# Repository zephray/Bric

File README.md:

Bric
====

Bric is the codename for my course project design for EE-300 at Penn State. It is a portable digital audio player. It was evolved from my previous project RhythmPocketLite, and the code has been used as base for my next project called Fobu. The code hosted here is likely broken and won't compile and is only here for archive purposes.

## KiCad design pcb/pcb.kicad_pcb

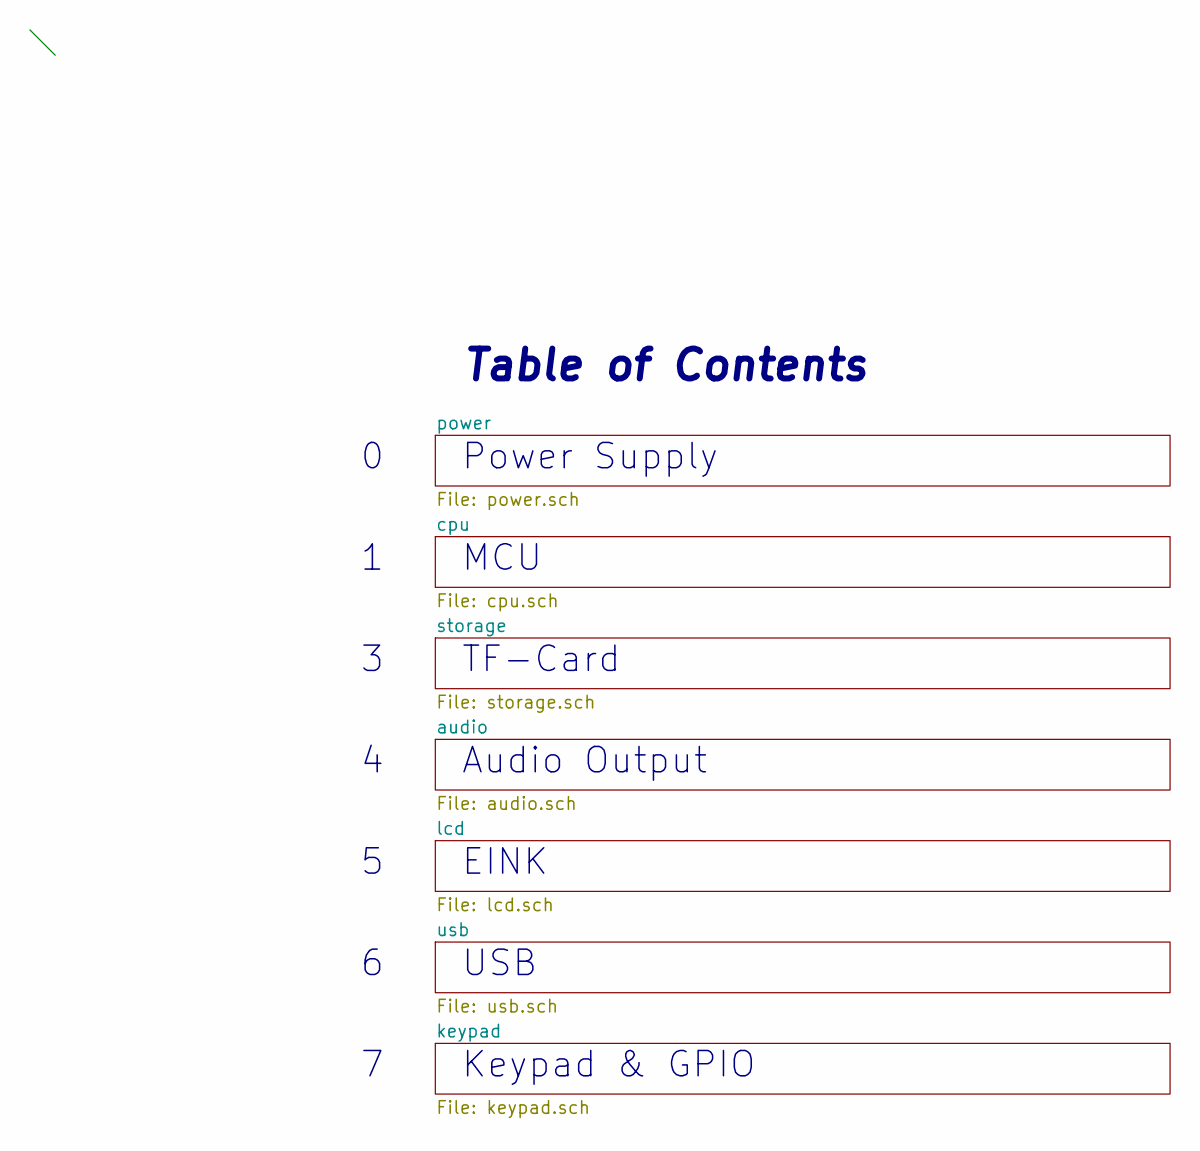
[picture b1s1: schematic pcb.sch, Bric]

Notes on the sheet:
MCU
EINK
TF-Card
Table of Contents
Power Supply
Audio Output
Keypad & GPIO
USB

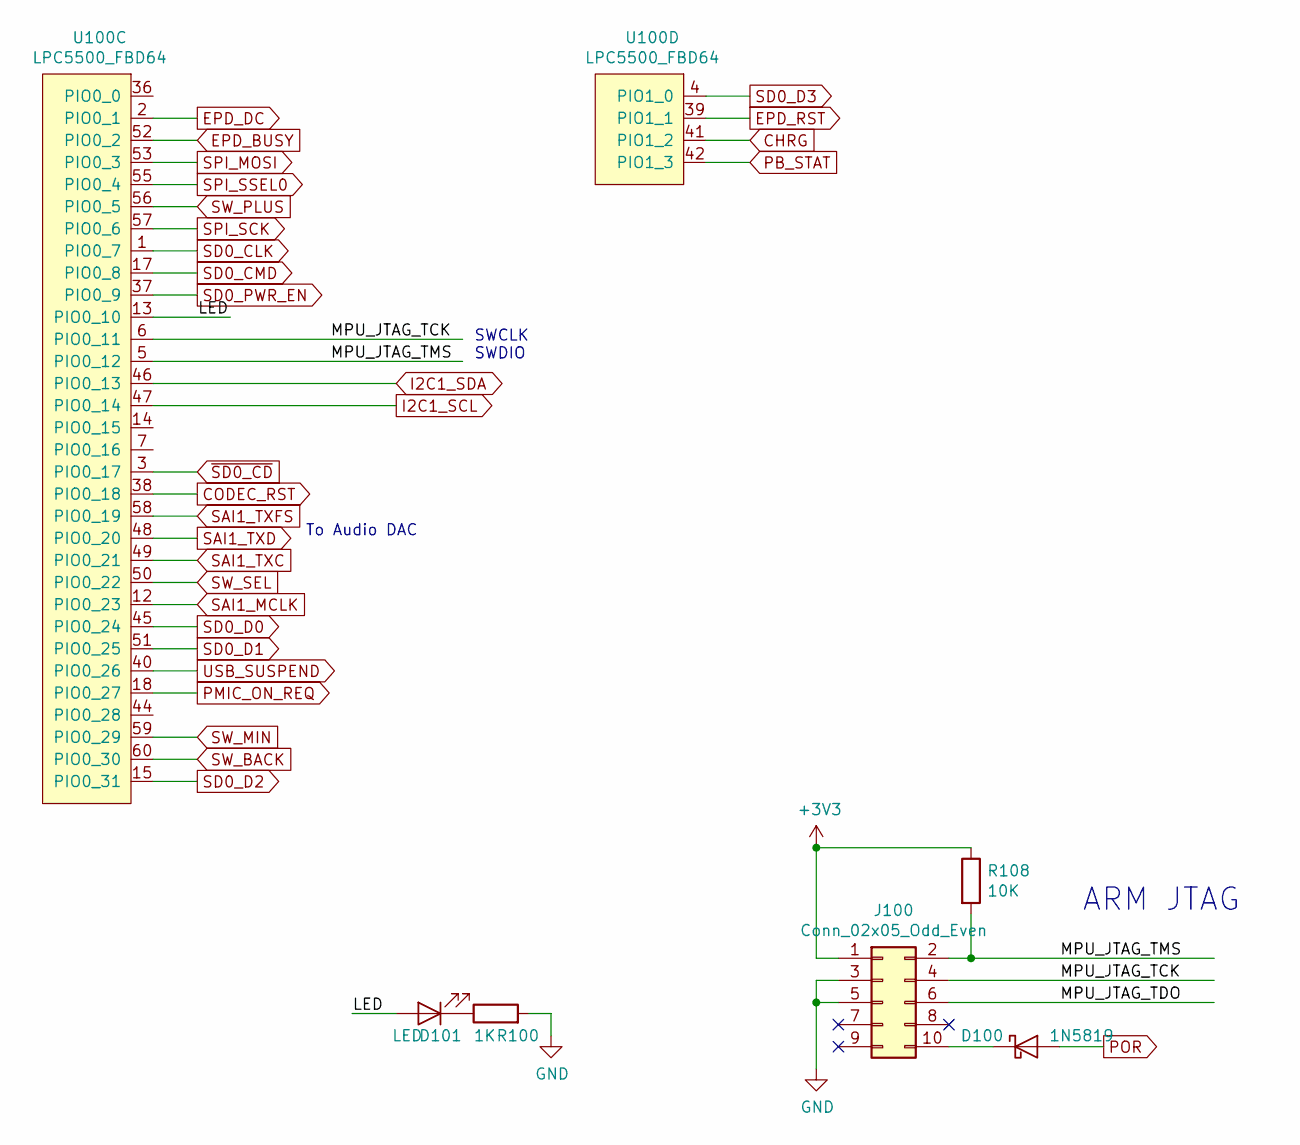
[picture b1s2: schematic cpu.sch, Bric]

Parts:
D100: 1N5819; D_SOD-123
D101: LED; LED_0603_1608Metric
J100: Conn_02x05_Odd_Even; PinHeader_2x05_P1.27mm_Vertical_SMD
R100: 1K; R_0603_1608Metric
R108: 10K; R_0603_1608Metric
U100: LPC5500_FBD64; LQFP-64-1EP_10x10mm_P0.5mm_EP5x5mm_ThermalVias

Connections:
/cpu/LED: D101.2 (A), U100.13 (PIO0_10)
/cpu/MPU_JTAG_TCK: J100.4, U100.6 (PIO0_11)
/cpu/MPU_JTAG_TMS: J100.2, R108.2, U100.5 (PIO0_12)
CHRG: U100.41 (PIO1_2); also elsewhere on the board
CODEC_RST: U100.38 (PIO0_18); also elsewhere on the board
EPD_BUSY: U100.52 (PIO0_2); also elsewhere on the board
EPD_DC: U100.2 (PIO0_1); also elsewhere on the board
EPD_RST: U100.39 (PIO1_1); also elsewhere on the board
I2C1_SCL: U100.47 (PIO0_14); also elsewhere on the board
I2C1_SDA: U100.46 (PIO0_13); also elsewhere on the board
unnamed: D100.1 (K), J100.10
unnamed: D101.1 (K), R100.1
PB_STAT: U100.42 (PIO1_3); also elsewhere on the board
PMIC_ON_REQ: U100.18 (PIO0_27); also elsewhere on the board
POR: D100.2 (A); also elsewhere on the board
SAI1_MCLK: U100.12 (PIO0_23); also elsewhere on the board
SAI1_TXC: U100.49 (PIO0_21); also elsewhere on the board
SAI1_TXD: U100.48 (PIO0_20); also elsewhere on the board
SAI1_TXFS: U100.58 (PIO0_19); also elsewhere on the board
SD0_CLK: U100.1 (PIO0_7); also elsewhere on the board
SD0_CMD: U100.17 (PIO0_8); also elsewhere on the board
SD0_D0: U100.45 (PIO0_24); also elsewhere on the board
SD0_D1: U100.51 (PIO0_25); also elsewhere on the board
SD0_D2: U100.15 (PIO0_31); also elsewhere on the board
SD0_D3: U100.4 (PIO1_0); also elsewhere on the board
SPI_MOSI: U100.53 (PIO0_3); also elsewhere on the board
SPI_SCK: U100.57 (PIO0_6); also elsewhere on the board
SPI_SSEL0: U100.55 (PIO0_4); also elsewhere on the board
SW_BACK: U100.60 (PIO0_30); also elsewhere on the board
SW_MIN: U100.59 (PIO0_29); also elsewhere on the board
SW_PLUS: U100.56 (PIO0_5); also elsewhere on the board
SW_SEL: U100.50 (PIO0_22); also elsewhere on the board
USB_SUSPEND: U100.40 (PIO0_26); also elsewhere on the board
~SD0_CD: U100.3 (PIO0_17); also elsewhere on the board

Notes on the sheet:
ARM JTAG
To Audio DAC
SWCLK SWDIO

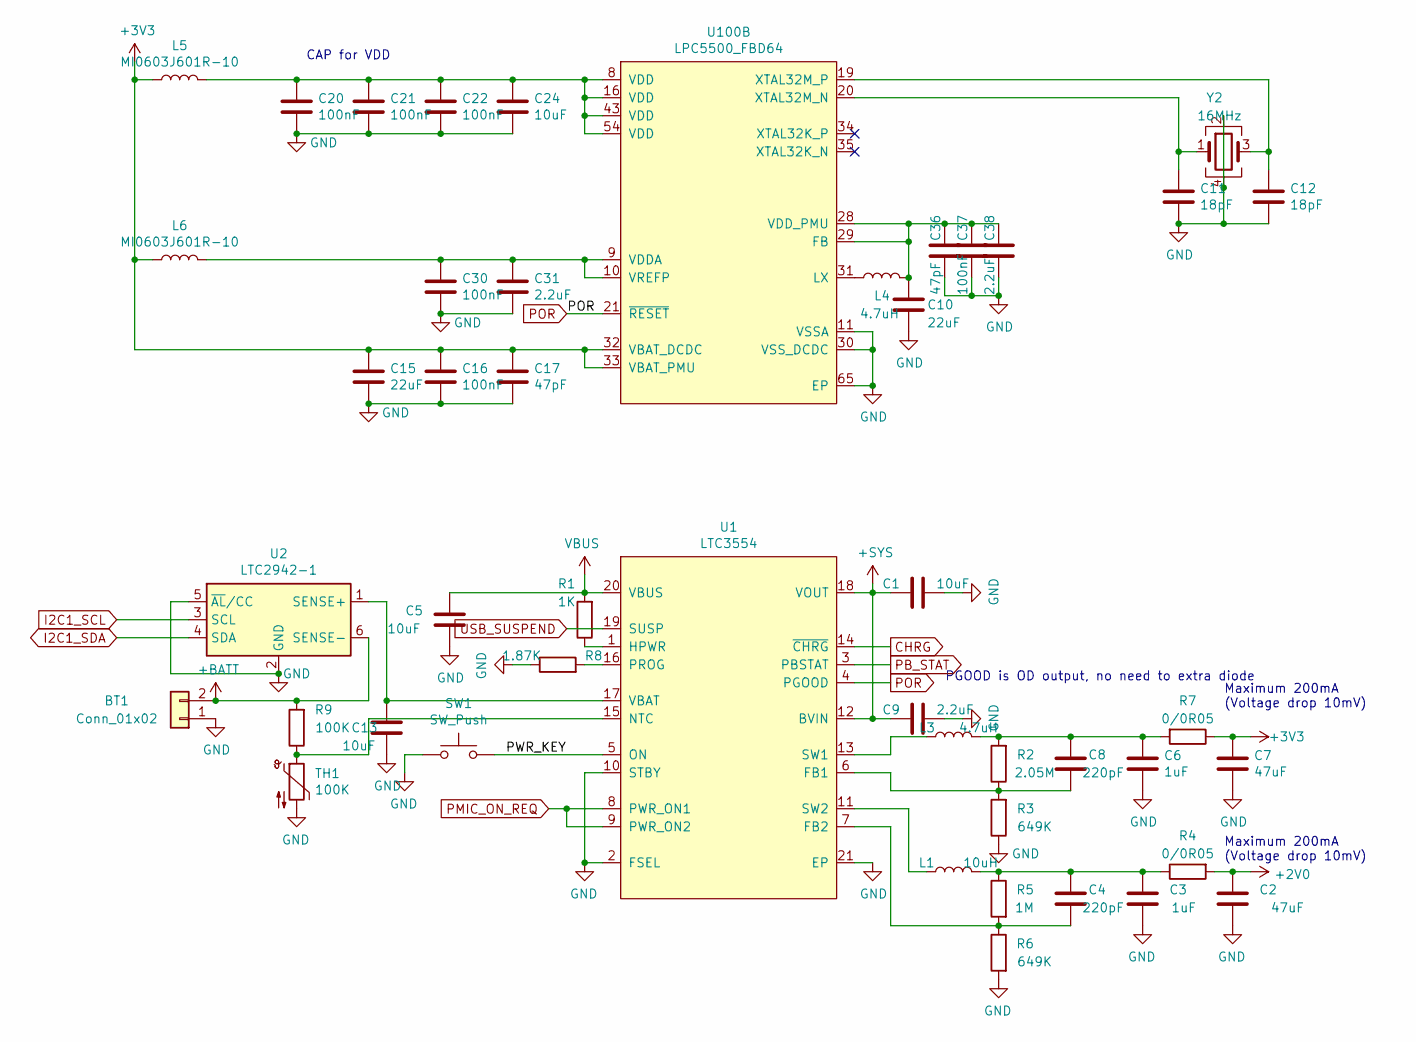
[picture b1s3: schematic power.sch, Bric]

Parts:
BT1: Conn_01x02; Molex_PicoBlade_53261-0271_1x02-1MP_P1.25mm_Horizontal
C1, C5, C13, C24: 10uF; C_0603_1608Metric
C2, C7: 47uF; C_0805_2012Metric
C3, C6: 1uF; C_0402_1005Metric
C4, C8: 220pF; C_0402_1005Metric
C9, C31, C38: 2.2uF; C_0402_1005Metric
C10, C15: 22uF; C_0603_1608Metric
C11, C12: 18pF; C_0402_1005Metric
C16, C20, C21, C22, C30, C37: 100nF; C_0402_1005Metric
C17, C36: 47pF; C_0402_1005Metric
L1: 10uH; L_Vishay_IHLP-1212
L3, L4: 4.7uH; L_Vishay_IHLP-1212
L5, L6: MI0603J601R-10; L_0603_1608Metric
R1: 1K; R_0603_1608Metric
R2: 2.05M; R_0603_1608Metric
R3, R6: 649K; R_0603_1608Metric
R4, R7: 0/0R05; R_0805_2012Metric
R5: 1M; R_0603_1608Metric
R8: 1.87K; R_0603_1608Metric
R9: 100K; R_0603_1608Metric
SW1: SW_Push; SW_SPST_EVQP7C
TH1: 100K; R_0603_1608Metric
U1: LTC3554; VQFN-20-1EP_3x3mm_P0.4mm_EP1.7x1.7mm_ThermalVias
U2: LTC2942-1; DFN-6-1EP_3x2mm_P0.5mm_EP1.65x1.35mm
U100: LPC5500_FBD64; LQFP-64-1EP_10x10mm_P0.5mm_EP5x5mm_ThermalVias
Y2: 16MHz; Oscillator_SMD_Abracon_ASE-4Pin_3.2x2.5mm

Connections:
+2V0: C2.1, R4.2; also elsewhere on the board
+BATT: BT1.2, R9.2, U2.6 (SENSE-)
+SYS: C1.2, C9.2, U1.12 (BVIN), U1.18 (VOUT); also elsewhere on the board
/power/PWR_KEY: SW1.2, U1.5 (ON)
CHRG: U1.14 (~CHRG); also elsewhere on the board
I2C1_SCL: U2.3 (SCL); also elsewhere on the board
I2C1_SDA: U2.4 (SDA); also elsewhere on the board
unnamed: C3.1, C4.1, L1.1, R4.1, R5.1
unnamed: C4.2, R5.2, R6.1, U1.7 (FB2)
unnamed: C6.1, C8.1, L3.2, R2.2, R7.2
unnamed: C8.2, R2.1, R3.2, U1.6 (FB1)
unnamed: C10.1, C36.1, C37.1, C38.1, L4.2, U100.28 (VDD_PMU), U100.29 (FB)
unnamed: C11.1, U100.20 (XTAL32M_N), Y2.1
unnamed: C12.1, U100.19 (XTAL32M_P), Y2.3
unnamed: C13.1, U1.17 (VBAT), U2.1 (SENSE+)
unnamed: C20.1, C21.1, C22.1, C24.1, L5.2, U100.8 (VDD), U100.16 (VDD), U100.43 (VDD), U100.54 (VDD)
unnamed: C30.1, C31.1, L6.2, U100.9 (VDDA), U100.10 (VREFP)
unnamed: L1.2, U1.11 (SW2)
unnamed: L3.1, U1.13 (SW1)
unnamed: L4.1, U100.31 (LX)
unnamed: R1.1, U1.1 (HPWR)
unnamed: R8.2, U1.16 (PROG)
unnamed: R9.1, TH1.1, U1.15 (NTC)
PB_STAT: U1.3 (PBSTAT); also elsewhere on the board
PMIC_ON_REQ: U1.8 (PWR_ON1), U1.9 (PWR_ON2); also elsewhere on the board
POR: U1.4 (PGOOD), U100.21 (~RESET); also elsewhere on the board
USB_SUSPEND: U1.19 (SUSP); also elsewhere on the board
VBUS: C5.1, R1.2, U1.20 (VBUS); also elsewhere on the board

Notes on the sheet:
Maximum 200mA (Voltage drop 10mV)
CAP for VDD
PGOOD is OD output, no need to extra diode

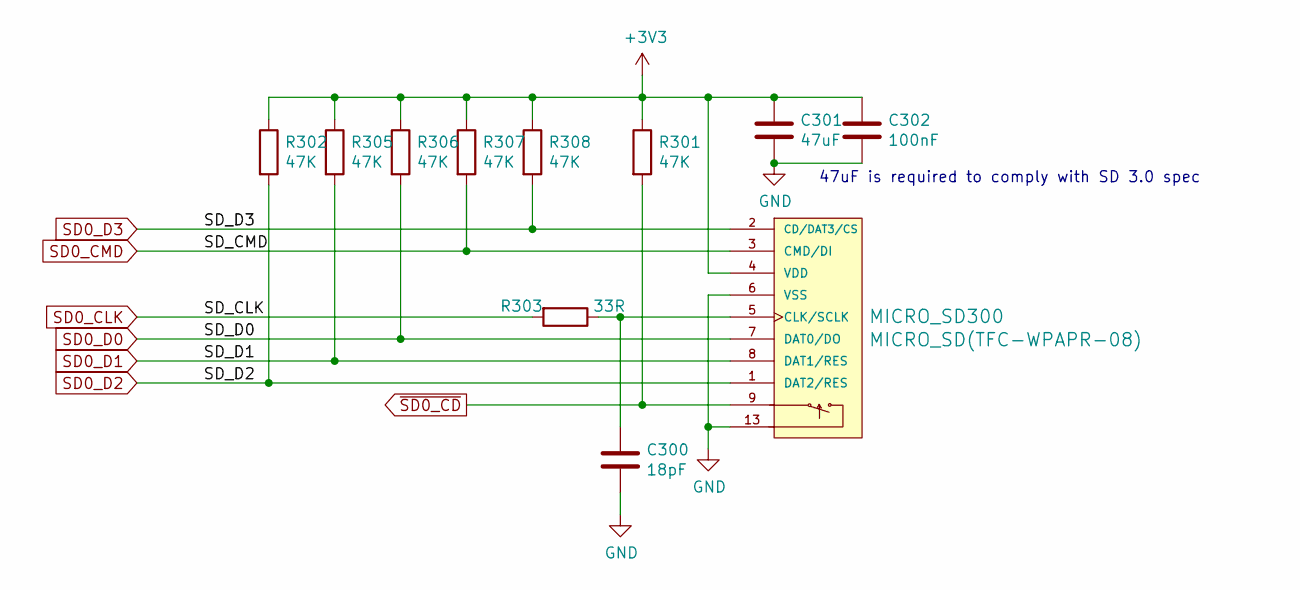
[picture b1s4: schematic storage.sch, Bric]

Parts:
C300: 18pF; C_0402_1005Metric
C301: 47uF; C_0805_2012Metric
C302: 100nF; C_0402_1005Metric
MICRO_SD300: MICRO_SD(TFC-WPAPR-08); TFC-WPAPR-08
R301, R302, R305, R306, R307, R308: 47K; R_0402_1005Metric
R303: 33R; R_0402_1005Metric

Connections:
unnamed: C300.1, MICRO_SD300.5 (CLK/SCLK), R303.1
SD0_CLK: R303.2; also elsewhere on the board
SD0_CMD: MICRO_SD300.3 (CMD/DI), R307.2; also elsewhere on the board
SD0_D0: MICRO_SD300.7 (DAT0/DO), R306.2; also elsewhere on the board
SD0_D1: MICRO_SD300.8 (DAT1/RES), R305.2; also elsewhere on the board
SD0_D2: MICRO_SD300.1 (DAT2/RES), R302.2; also elsewhere on the board
SD0_D3: MICRO_SD300.2 (CD/DAT3/CS), R308.2; also elsewhere on the board
~SD0_CD: MICRO_SD300.9, R301.2; also elsewhere on the board

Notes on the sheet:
47uF is required to comply with SD 3.0 spec

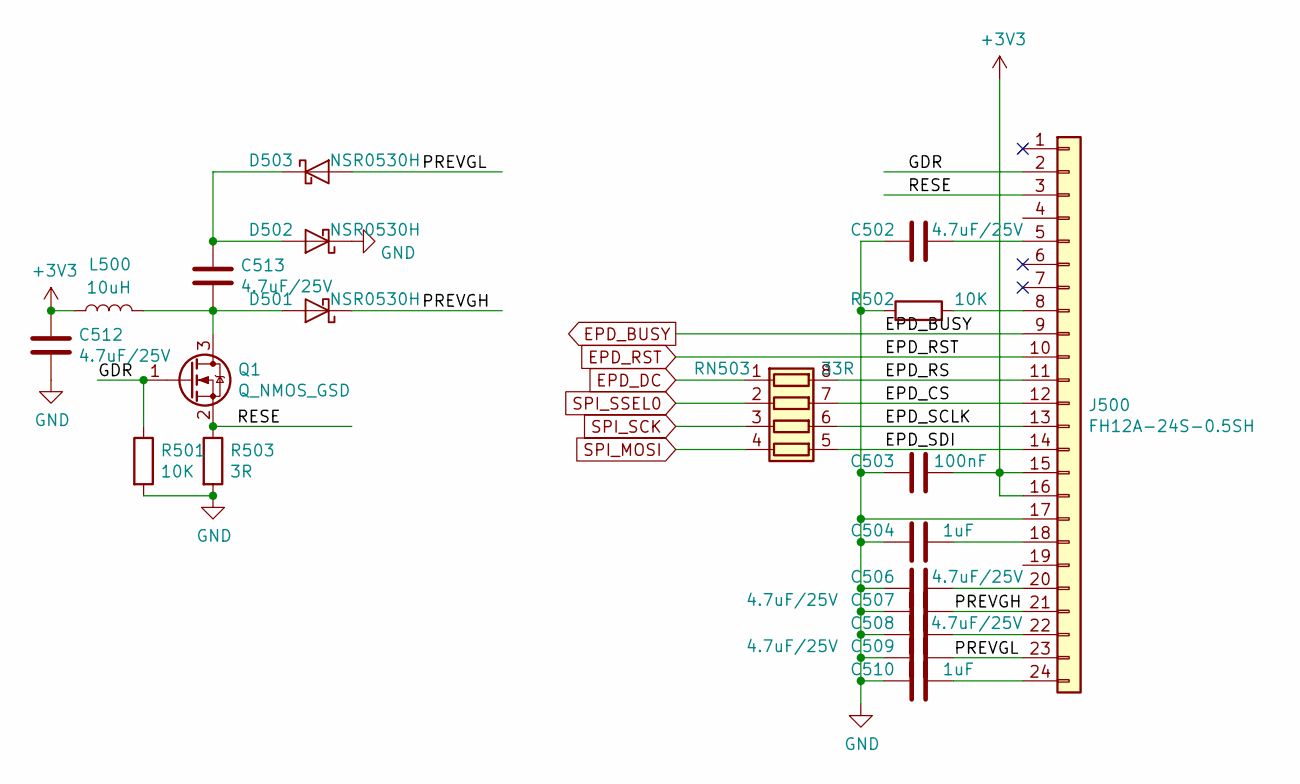
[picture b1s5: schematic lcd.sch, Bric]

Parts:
C502, C506, C507, C508, C509, C512, C513: 4.7uF/25V; C_0805_2012Metric
C503: 100nF; C_0402_1005Metric
C504, C510: 1uF; C_0603_1608Metric
D501, D502, D503: NSR0530H; D_SOD-323
J500: FH12A-24S-0.5SH; Hirose_FH12A-24S-0.5SH_1x24-1MP_P0.50mm_Horizontal
L500: 10uH; L_Vishay_IHLP-1212
Q1: Q_NMOS_GSD; SOT-323_SC-70
R501, R502: 10K; R_0603_1608Metric
R503: 3R; R_0603_1608Metric
RN503: 33R; R_Array_Convex_4x0402

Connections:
/lcd/EPD_CS: J500.12, RN503.7 (R2.2)
/lcd/EPD_RS: J500.11, RN503.8 (R1.2)
/lcd/EPD_SCLK: J500.13, RN503.6 (R3.2)
/lcd/EPD_SDI: J500.14, RN503.5 (R4.2)
/lcd/GDR: J500.2, Q1.1 (G), R501.1
/lcd/PREVGH: C507.2, D501.1 (K), J500.21
/lcd/PREVGL: C509.1, D503.2 (A), J500.23
/lcd/RESE: J500.3, Q1.2 (S), R503.1
EPD_BUSY: J500.9; also elsewhere on the board
EPD_DC: RN503.1 (R1.1); also elsewhere on the board
EPD_RST: J500.10; also elsewhere on the board
unnamed: C502.2, J500.5
unnamed: C504.2, J500.18
unnamed: C506.2, J500.20
unnamed: C508.1, J500.22
unnamed: C510.1, J500.24
unnamed: C513.1, D501.2 (A), L500.2, Q1.3 (D)
unnamed: C513.2, D502.2 (A), D503.1 (K)
unnamed: J500.8, R502.2
SPI_MOSI: RN503.4 (R4.1); also elsewhere on the board
SPI_SCK: RN503.3 (R3.1); also elsewhere on the board
SPI_SSEL0: RN503.2 (R2.1); also elsewhere on the board

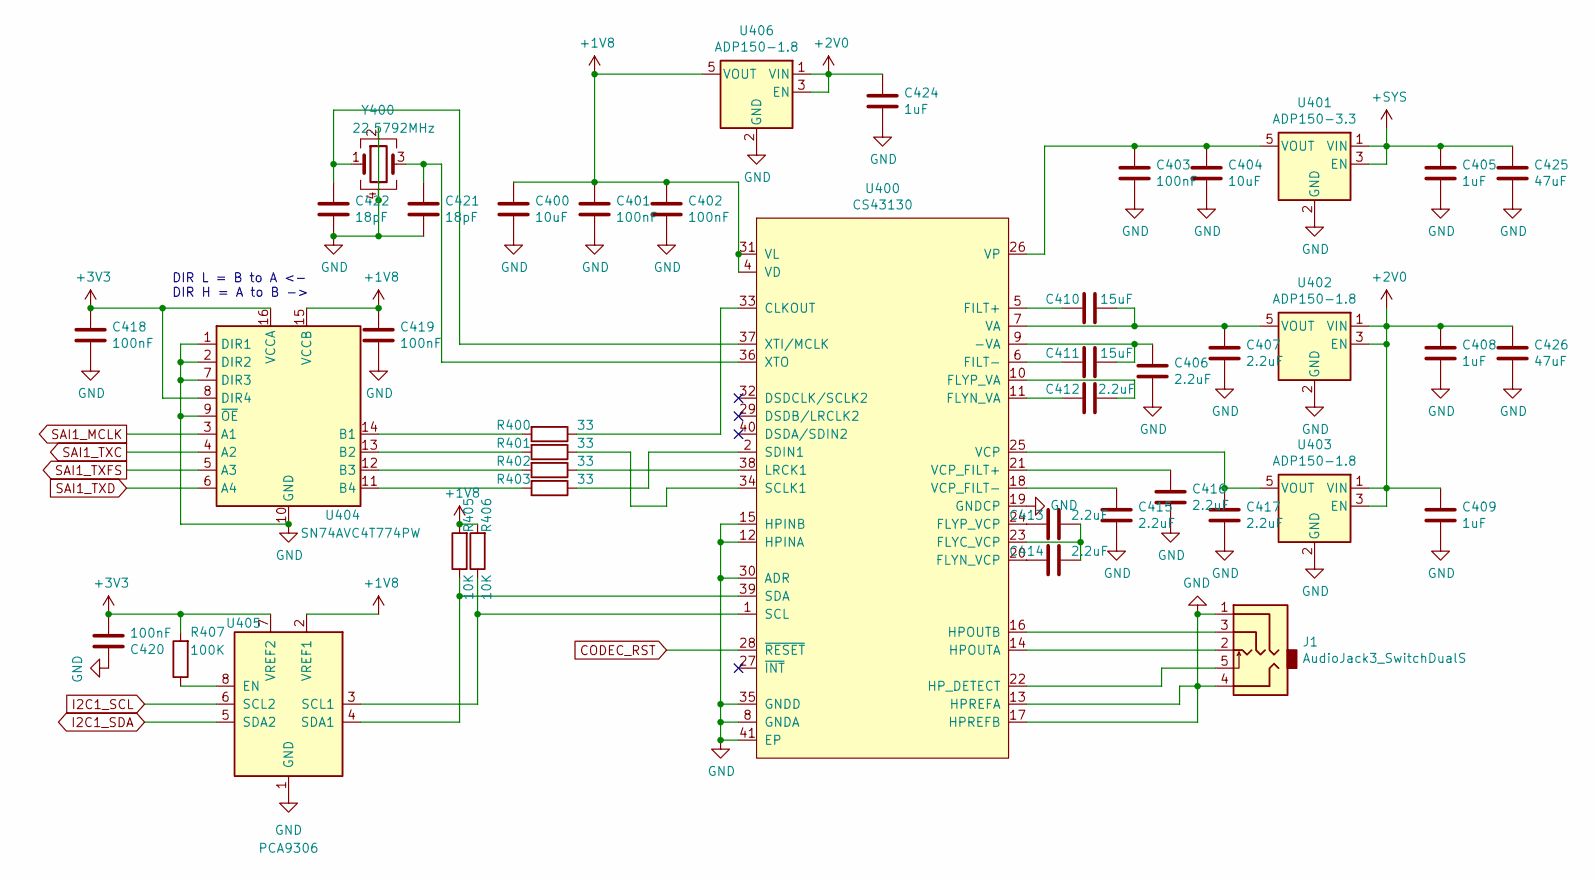
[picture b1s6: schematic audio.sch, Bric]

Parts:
C400: 10uF; C_0402_1005Metric
C401, C402, C403, C418, C419, C420: 100nF; C_0402_1005Metric
C404: 10uF; C_0603_1608Metric
C405, C408, C409, C424: 1uF; C_0402_1005Metric
C406, C407, C412, C413, C414, C415, C416, C417: 2.2uF; C_0402_1005Metric
C410, C411: 15uF; C_0603_1608Metric
C421, C422: 18pF; C_0402_1005Metric
C425, C426: 47uF; C_0805_2012Metric
J1: AudioJack3_SwitchDualS; Jack_3.5mm_PJ327E_5A
R400, R401, R402, R403: 33; R_0402_1005Metric
R405, R406: 10K; R_0603_1608Metric
R407: 100K; R_0603_1608Metric
U400: CS43130; QFN-40-1EP_5x5mm_P0.4mm_EP3.6x3.6mm_ThermalVias
U401: ADP150-3.3; SOT-23-5
U402, U403, U406: ADP150-1.8; SOT-23-5
U404: SN74AVC4T774PW; TSSOP-16_4.4x5mm_P0.65mm
U405: PCA9306; VSSOP-8_2.3x2mm_P0.5mm
Y400: 22.5792MHz; Oscillator_SMD_Abracon_ASE-4Pin_3.2x2.5mm

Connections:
+1V8: C400.1, C401.1, C402.1, C419.1, R405.2, R406.2, U400.4 (VD), U400.31 (VL), U404.15 (VCCB), U405.2 (VREF1), U406.5 (VOUT)
+2V0: C408.1, C409.1, C424.1, C426.1, U402.1 (VIN), U402.3 (EN), U403.1 (VIN), U403.3 (EN), U406.1 (VIN), U406.3 (EN); also elsewhere on the board
+SYS: C405.1, C425.1, U401.1 (VIN), U401.3 (EN); also elsewhere on the board
CODEC_RST: U400.28 (~RESET); also elsewhere on the board
I2C1_SCL: U405.6 (SCL2); also elsewhere on the board
I2C1_SDA: U405.5 (SDA2); also elsewhere on the board
unnamed: C403.1, C404.1, U400.26 (VP), U401.5 (VOUT)
unnamed: C406.1, C411.1, U400.9 (-VA)
unnamed: C407.1, C410.1, U400.7 (VA), U402.5 (VOUT)
unnamed: C410.2, U400.5 (FILT+)
unnamed: C411.2, U400.6 (FILT-)
unnamed: C412.1, U400.10 (FLYP_VA)
unnamed: C412.2, U400.11 (FLYN_VA)
unnamed: C413.1, C414.1, U400.23 (FLYC_VCP)
unnamed: C413.2, U400.24 (FLYP_VCP)
unnamed: C414.2, U400.20 (FLYN_VCP)
unnamed: C415.1, U400.18 (VCP_FILT-)
unnamed: C416.1, U400.21 (VCP_FILT+)
unnamed: C417.1, U400.25 (VCP), U403.5 (VOUT)
unnamed: C421.1, U400.36 (XTO), Y400.3
unnamed: C422.1, U400.37 (XTI/MCLK), Y400.1
unnamed: J1.2, U400.14 (HPOUTA)
unnamed: J1.3, U400.16 (HPOUTB)
unnamed: J1.5, U400.22 (HP_DETECT)
unnamed: R400.1, U400.33 (CLKOUT)
unnamed: R400.2, U404.14 (B1)
unnamed: R401.1, U400.34 (SCLK1)
unnamed: R401.2, U404.13 (B2)
unnamed: R402.1, U400.38 (LRCK1)
unnamed: R402.2, U404.12 (B3)
unnamed: R403.1, U400.2 (SDIN1)
unnamed: R403.2, U404.11 (B4)
unnamed: R405.1, U400.39 (SDA), U405.4 (SDA1)
unnamed: R406.1, U400.1 (SCL), U405.3 (SCL1)
unnamed: R407.1, U405.8 (EN)
SAI1_MCLK: U404.3 (A1); also elsewhere on the board
SAI1_TXC: U404.4 (A2); also elsewhere on the board
SAI1_TXD: U404.6 (A4); also elsewhere on the board
SAI1_TXFS: U404.5 (A3); also elsewhere on the board

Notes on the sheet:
DIR L = B to A <- DIR H = A to B ->

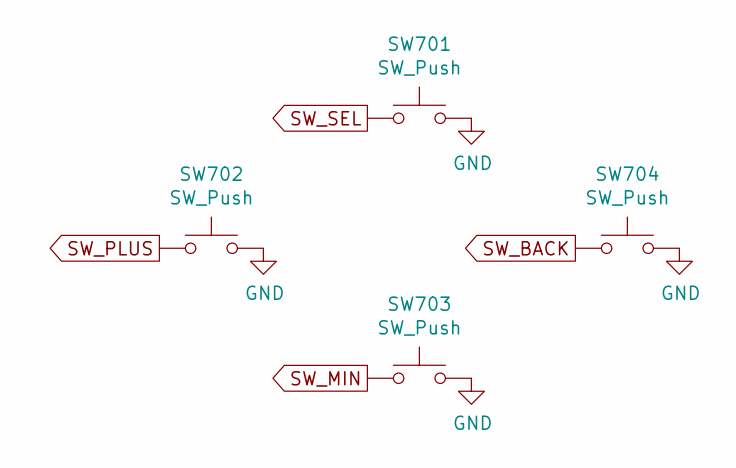
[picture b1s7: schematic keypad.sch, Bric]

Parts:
SW701, SW702, SW703, SW704: SW_Push; SW_SPST_EVQP7C

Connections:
SW_BACK: SW704.1; also elsewhere on the board
SW_MIN: SW703.1; also elsewhere on the board
SW_PLUS: SW702.1; also elsewhere on the board
SW_SEL: SW701.1; also elsewhere on the board

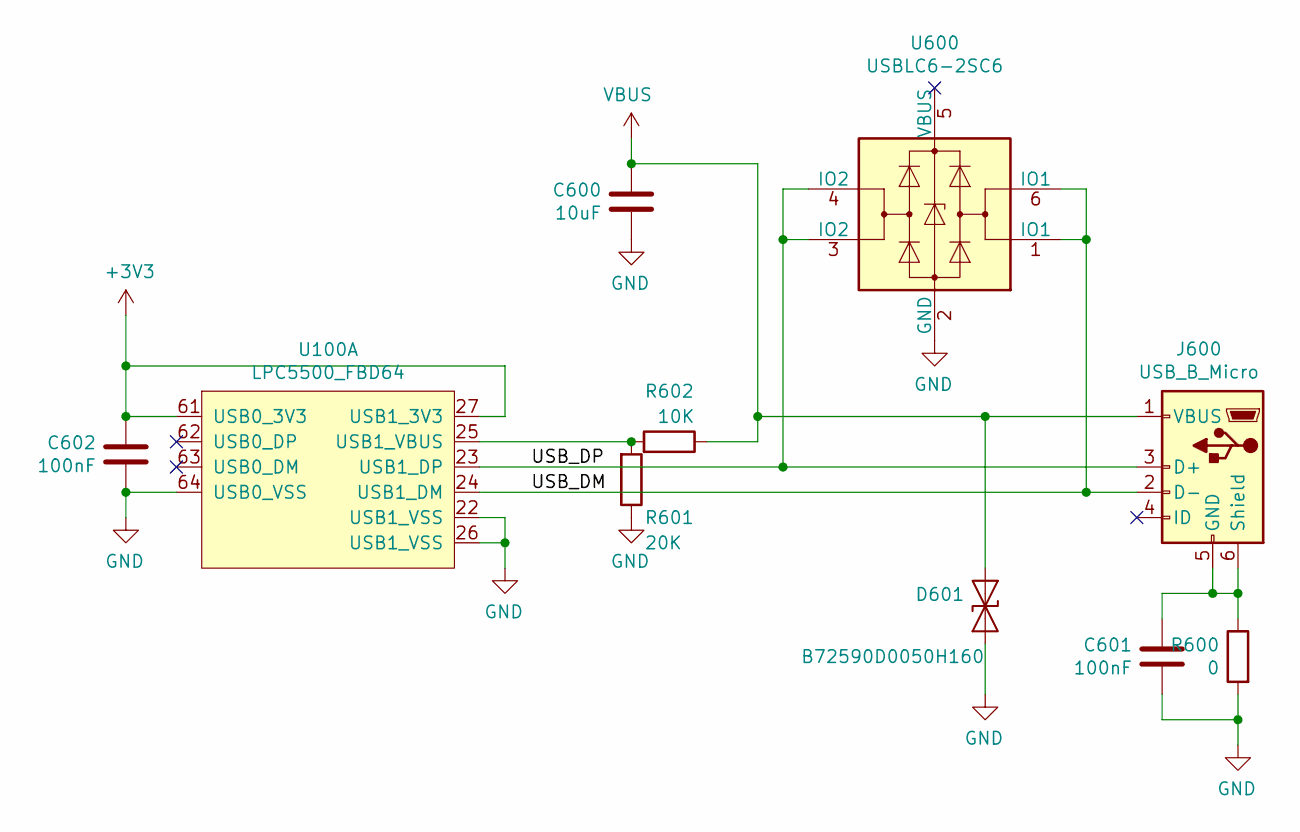
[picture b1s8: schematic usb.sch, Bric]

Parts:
C600: 10uF; C_0603_1608Metric
C601: 100nF; C_0805_2012Metric
C602: 100nF; C_0402_1005Metric
D601: B72590D0050H160; D_0402_1005Metric
J600: USB_B_Micro; USB_Micro-B_Amphenol_10103594-0001LF_Horizontal
R600: 0; R_0805_2012Metric
R601: 20K; R_0603_1608Metric
R602: 10K; R_0603_1608Metric
U100: LPC5500_FBD64; LQFP-64-1EP_10x10mm_P0.5mm_EP5x5mm_ThermalVias
U600: USBLC6-2SC6; SOT-23-6

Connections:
/usb/USB_DM: J600.2 (D-), U100.24 (USB1_DM), U600.1 (IO1), U600.6 (IO1)
/usb/USB_DP: J600.3 (D+), U100.23 (USB1_DP), U600.3 (IO2), U600.4 (IO2)
unnamed: C601.1, J600.5 (GND), J600.6 (Shield), R600.1
unnamed: R601.2, R602.2, U100.25 (USB1_VBUS)
VBUS: C600.1, D601.1 (A1), J600.1 (VBUS), R602.1; also elsewhere on the board

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
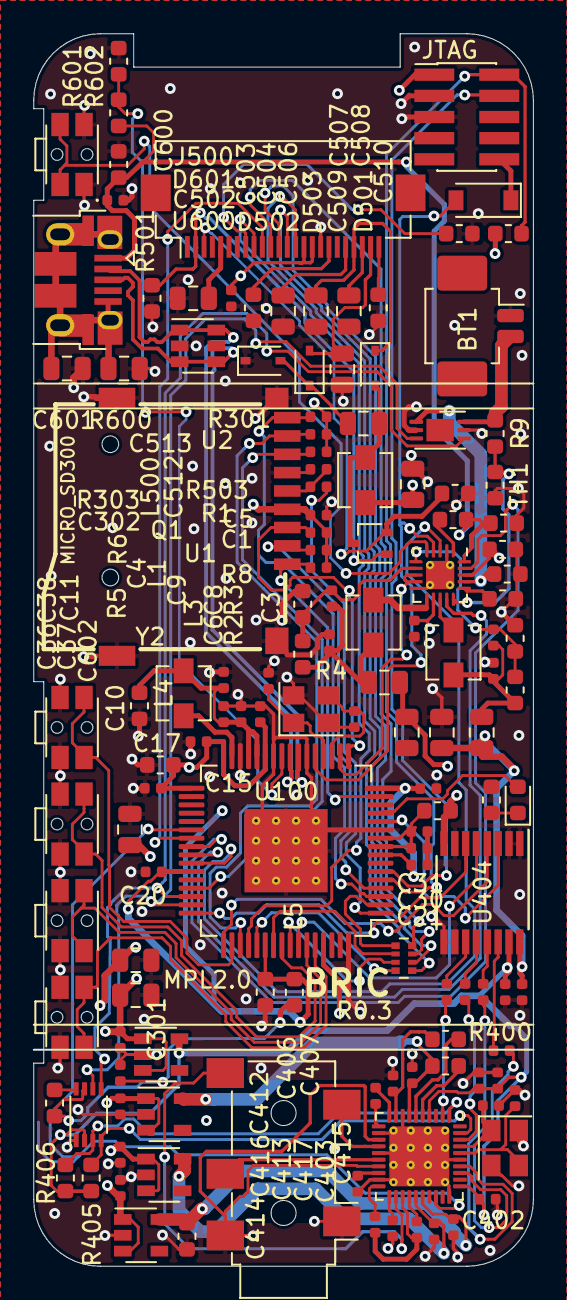
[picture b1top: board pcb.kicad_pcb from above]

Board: 4 copper layers, 30.0 x 74.0 mm, 137 parts (0 on the bottom side), 108 nets.

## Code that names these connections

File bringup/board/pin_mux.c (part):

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mcu_data: ksdk2_0
processor_version: 7.0.1
pin_labels:
- {pin_num: '2', pin_signal: PIO0_1/FC3_CTS_SDA_SSEL0/CT_INP0/SCT_GPI1/SD1_CLK/CMP0_OUT/SECURE_GPIO0_1, label: EPD_DC, identifier: EPD_DC}
- {pin_num: '12', pin_signal: PIO0_23/MCLK/CTIMER1_MAT2/CTIMER3_MAT3/SCT0_OUT4/FC0_CTS_SDA_SSEL0/SD1_D1/SECURE_GPIO0_23/ADC0_0, label: MCLK, identifier: MCLK}
- {pin_num: '50', pin_signal: PIO0_22/FC6_TXD_SCL_MISO_WS/UTICK_CAP1/CT_INP15/SCT0_OUT3/USB0_VBUS/SD1_D0/PLU_OUT7/SECURE_GPIO0_22, label: SW_SEL, identifier: SW_;SW_SEL}
- {pin_num: '52', pin_signal: PIO0_2/FC3_TXD_SCL_MISO_WS/CT_INP1/SCT0_OUT0/SCT_GPI2/SECURE_GPIO0_2, label: EPD_BUSY, identifier: EPD_BUSY}
- {pin_num: '56', pin_signal: PIO0_5/FC4_RXD_SDA_MOSI_DATA/CTIMER3_MAT0/SCT_GPI5/FC3_RTS_SCL_SSEL1/MCLK/SECURE_GPIO0_5, label: SW_PLUS, identifier: SW_PLUS}
- {pin_num: '59', pin_signal: PIO0_29/FC0_RXD_SDA_MOSI_DATA/SD1_D2/CTIMER2_MAT3/SCT0_OUT8/CMP0_OUT/PLU_OUT2/SECURE_GPIO0_29, label: SW_MIN, identifier: SW_MIN}
- {pin_num: '60', pin_signal: PIO0_30/FC0_TXD_SCL_MISO_WS/SD1_D3/CTIMER0_MAT0/SCT0_OUT9/SECURE_GPIO0_30, label: SW_BACK, identifier: SW_BACK}
- {pin_num: '13', pin_signal: PIO0_10/FC6_SCK/CT_INP10/CTIMER2_MAT0/FC1_TXD_SCL_MISO_WS/SCT0_OUT2/SWO/SECURE_GPIO0_10/ADC0_1, label: LED, identifier: LED}
- {pin_num: '18', pin_signal: PIO0_27/FC2_TXD_SCL_MISO_WS/CTIMER3_MAT2/SCT0_OUT6/FC7_RXD_SDA_MOSI_DATA/PLU_OUT0/SECURE_GPIO0_27, label: PMIC_ON_REQ, identifier: PMIC_ON_REQ}
- {pin_num: '38', pin_signal: PIO0_18/FC4_CTS_SDA_SSEL0/SD0_WR_PRT/CTIMER1_MAT0/SCT0_OUT1/PLU_IN3/SECURE_GPIO0_18/ACMP0_C, label: CODEC_RST, identifier: CODEC_RST}
- {pin_num: '40', pin_signal: PIO0_26/FC2_RXD_SDA_MOSI_DATA/CLKOUT/CT_INP14/SCT0_OUT5/USB0_IDVALUE/FC0_SCK/HS_SPI_MOSI/SECURE_GPIO0_26, label: USB_SUSPEND, identifier: USB_SUSPEND}
- {pin_num: '41', pin_signal: PIO1_2/CTIMER0_MAT3/SCT_GPI6/HS_SPI_SCK/USB1_PORTPWRN/PLU_OUT5, label: CHRG, identifier: CHRG}
- {pin_num: '42', pin_signal: PIO1_3/SCT0_OUT4/HS_SPI_MISO/USB0_PORTPWRN/PLU_OUT6, label: PB_STAT, identifier: PB_STAT}
- {pin_num: '37', pin_signal: PIO0_9/FC3_SSEL2/SD0_POW_EN/FC5_TXD_SCL_MISO_WS/SECURE_GPIO0_9/ACMP0_B, label: SD_PWR_EN, identifier: SD_PWR_eN;SD_PWR_EN}
- {pin_num: '39', pin_signal: PIO1_1/FC3_RXD_SDA_MOSI_DATA/CT_INP3/SCT_GPI5/HS_SPI_SSEL1/USB1_OVERCURRENTN/PLU_OUT4, label: EPD_RST, identifier: EPD_RST}
 * BE CAREFUL MODIFYING THIS COMMENT - IT IS YAML SETTINGS FOR TOOLS ***********
 */
/* clang-format on */
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BOARD_InitPins:
- options: {callFromInitBoot: 'true', coreID: cm33_core0, enableClock: 'true'}
- pin_list:
  - {pin_num: '1', peripheral: SDIF, signal: SD0_CLK, pin_signal: PIO0_7/FC3_RTS_SCL_SSEL1/SD0_CLK/FC5_SCK/FC1_SCK/SECURE_GPIO0_7, slew_rate: fast}
  - {pin_num: '17', peripheral: SDIF, signal: SD0_CMD, pin_signal: PIO0_8/FC3_SSEL3/SD0_CMD/FC5_RXD_SDA_MOSI_DATA/SWO/SECURE_GPIO0_8, slew_rate: fast}
  - {pin_num: '45', peripheral: SDIF, signal: 'SD0_D, 0', pin_signal: PIO0_24/FC0_RXD_SDA_MOSI_DATA/SD0_D0/CT_INP8/SCT_GPI0/SECURE_GPIO0_24, slew_rate: fast}
  - {pin_num: '51', peripheral: SDIF, signal: 'SD0_D, 1', pin_signal: PIO0_25/FC0_TXD_SCL_MISO_WS/SD0_D1/CT_INP9/SCT_GPI1/SECURE_GPIO0_25, slew_rate: fast}
  - {pin_num: '15', peripheral: SDIF, signal: 'SD0_D, 2', pin_signal: PIO0_31/FC0_CTS_SDA_SSEL0/SD0_D2/CTIMER0_MAT1/SCT0_OUT3/SECURE_GPIO0_31/ADC0_3, slew_rate: fast}
  - {pin_num: '4', peripheral: SDIF, signal: 'SD0_D, 3', pin_signal: PIO1_0/FC0_RTS_SCL_SSEL1/SD0_D3/CT_INP2/SCT_GPI4/PLU_OUT3/ADC0_11, slew_rate: fast}
  - {pin_num: '3', peripheral: SDIF, signal: SD0_CARD_DET, pin_signal: PIO0_17/FC4_SSEL2/SD0_CARD_DET_N/SCT_GPI7/SCT0_OUT0/SD0_CARD_INT_N/PLU_IN2/SECURE_GPIO0_17,
    invert: enabled}
  - {pin_num: '2', peripheral: GPIO, signal: 'PIO0, 1', pin_signal: PIO0_1/FC3_CTS_SDA_SSEL0/CT_INP0/SCT_GPI1/SD1_CLK/CMP0_OUT/SECURE_GPIO0_1, direction: OUTPUT}
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  - {pin_num: '37', peripheral: GPIO, signal: 'PIO0, 9', pin_signal: PIO0_9/FC3_SSEL2/SD0_POW_EN/FC5_TXD_SCL_MISO_WS/SECURE_GPIO0_9/ACMP0_B, identifier: SD_PWR_EN,
    direction: OUTPUT, gpio_init_state: 'true'}
  - {pin_num: '25', peripheral: USBHSH, signal: USB_VBUS, pin_signal: USB1_VBUS}
  - {pin_num: '24', peripheral: USBHSH, signal: USB_DM, pin_signal: USB1_DM}
  - {pin_num: '23', peripheral: USBHSH, signal: USB_DP, pin_signal: USB1_DP}
  - {pin_num: '39', peripheral: GPIO, signal: 'PIO1, 1', pin_signal: PIO1_1/FC3_RXD_SDA_MOSI_DATA/CT_INP3/SCT_GPI5/HS_SPI_SSEL1/USB1_OVERCURRENTN/PLU_OUT4, direction: OUTPUT,
    gpio_init_state: 'true'}
 * BE CAREFUL MODIFYING THIS COMMENT - IT IS YAML SETTINGS FOR TOOLS ***********
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                          (~(IOCON_PIO_FUNC_MASK | IOCON_PIO_SLEW_MASK | IOCON_PIO_DIGIMODE_MASK)))

                         /* Selects pin function.
                          * : PORT024 (pin 45) is configured as SD0_D0. */
                         | IOCON_PIO_FUNC(PIO0_24_FUNC_ALT2)

                         /* Driver slew rate.
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                          (~(IOCON_PIO_FUNC_MASK | IOCON_PIO_SLEW_MASK | IOCON_PIO_DIGIMODE_MASK)))

                         /* Selects pin function.
                          * : PORT025 (pin 51) is configured as SD0_D1. */
                         | IOCON_PIO_FUNC(PIO0_25_FUNC_ALT2)

                         /* Driver slew rate.
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                          (~(IOCON_PIO_FUNC_MASK | IOCON_PIO_SLEW_MASK | IOCON_PIO_DIGIMODE_MASK)))

                         /* Selects pin function.
                          * : PORT031 (pin 15) is configured as SD0_D2. */
                         | IOCON_PIO_FUNC(PIO0_31_FUNC_ALT2)

                         /* Driver slew rate.
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                         (~(IOCON_PIO_FUNC_MASK | IOCON_PIO_SLEW_MASK | IOCON_PIO_DIGIMODE_MASK)))

                        /* Selects pin function.
                         * : PORT07 (pin 1) is configured as SD0_CLK. */
                        | IOCON_PIO_FUNC(PIO0_7_FUNC_ALT2)

                        /* Driver slew rate.
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                         (~(IOCON_PIO_FUNC_MASK | IOCON_PIO_SLEW_MASK | IOCON_PIO_DIGIMODE_MASK)))

                        /* Selects pin function.
                         * : PORT08 (pin 17) is configured as SD0_CMD. */
                        | IOCON_PIO_FUNC(PIO0_8_FUNC_ALT2)

                        /* Driver slew rate.
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                         (~(IOCON_PIO_FUNC_MASK | IOCON_PIO_SLEW_MASK | IOCON_PIO_DIGIMODE_MASK)))

                        /* Selects pin function.
                         * : PORT10 (pin 4) is configured as SD0_D3. */
                        | IOCON_PIO_FUNC(PIO1_0_FUNC_ALT2)

                        /* Driver slew rate.
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
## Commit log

2020-03-10 finish sch rev 0.1
2020-03-11 assign footprints
2020-03-15 rev 0.1
2020-03-18 fw: import sdk
2020-03-19 fw: setting up pins and clock
2020-03-19 pcb: rename keypad signal names
2020-03-20 fw: initial epd, codec, sdcard bring up code
2020-03-24 pcb: bug fixes
2020-03-26 fw: bring up for r0p1
2020-03-30 pcb: rev 0.2
2020-04-11 usb audio working on rev 0.2
2020-04-11 rename original fw framework to bringup
2020-04-14 Start working on the new FreeRTOS based firmware
2020-04-21 start implementing power management and tag display
2020-07-26 pcb: rev 0.3
2020-08-05 fw: move mcu related stuff to dedicated folder
2020-08-05 gitignore: ignore vscode folder and test audio files
2020-08-05 firmware: initial linux port
2020-11-03 firmware: allow audio playback on linux
2020-11-04 Pull in local unstaged changes
2020-11-04 Add readme
2021-05-26 firmware: builds; support gb2312 12px/16px font
2021-06-10 fw: initial ui
2021-11-30 fw: initial input and power management framework; linux sim catchup
2021-11-30 fw: adapt id3v2lib to use new fs hal
2021-11-30 fw: initial file browser; target dummy power lib; target lib fixes
2021-12-01 fw: implement intiial song info display
2021-12-02 fw: initial batcal ui
2021-12-04 fw: support wav playback; support 32b sample in linux
2021-12-14 fw: reduce wav buffer size to allow playback on hw
